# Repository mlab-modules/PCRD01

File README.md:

# PCRD01B
Semiconcductor cosmic radiation detector Silicon diode analogue amplifier.

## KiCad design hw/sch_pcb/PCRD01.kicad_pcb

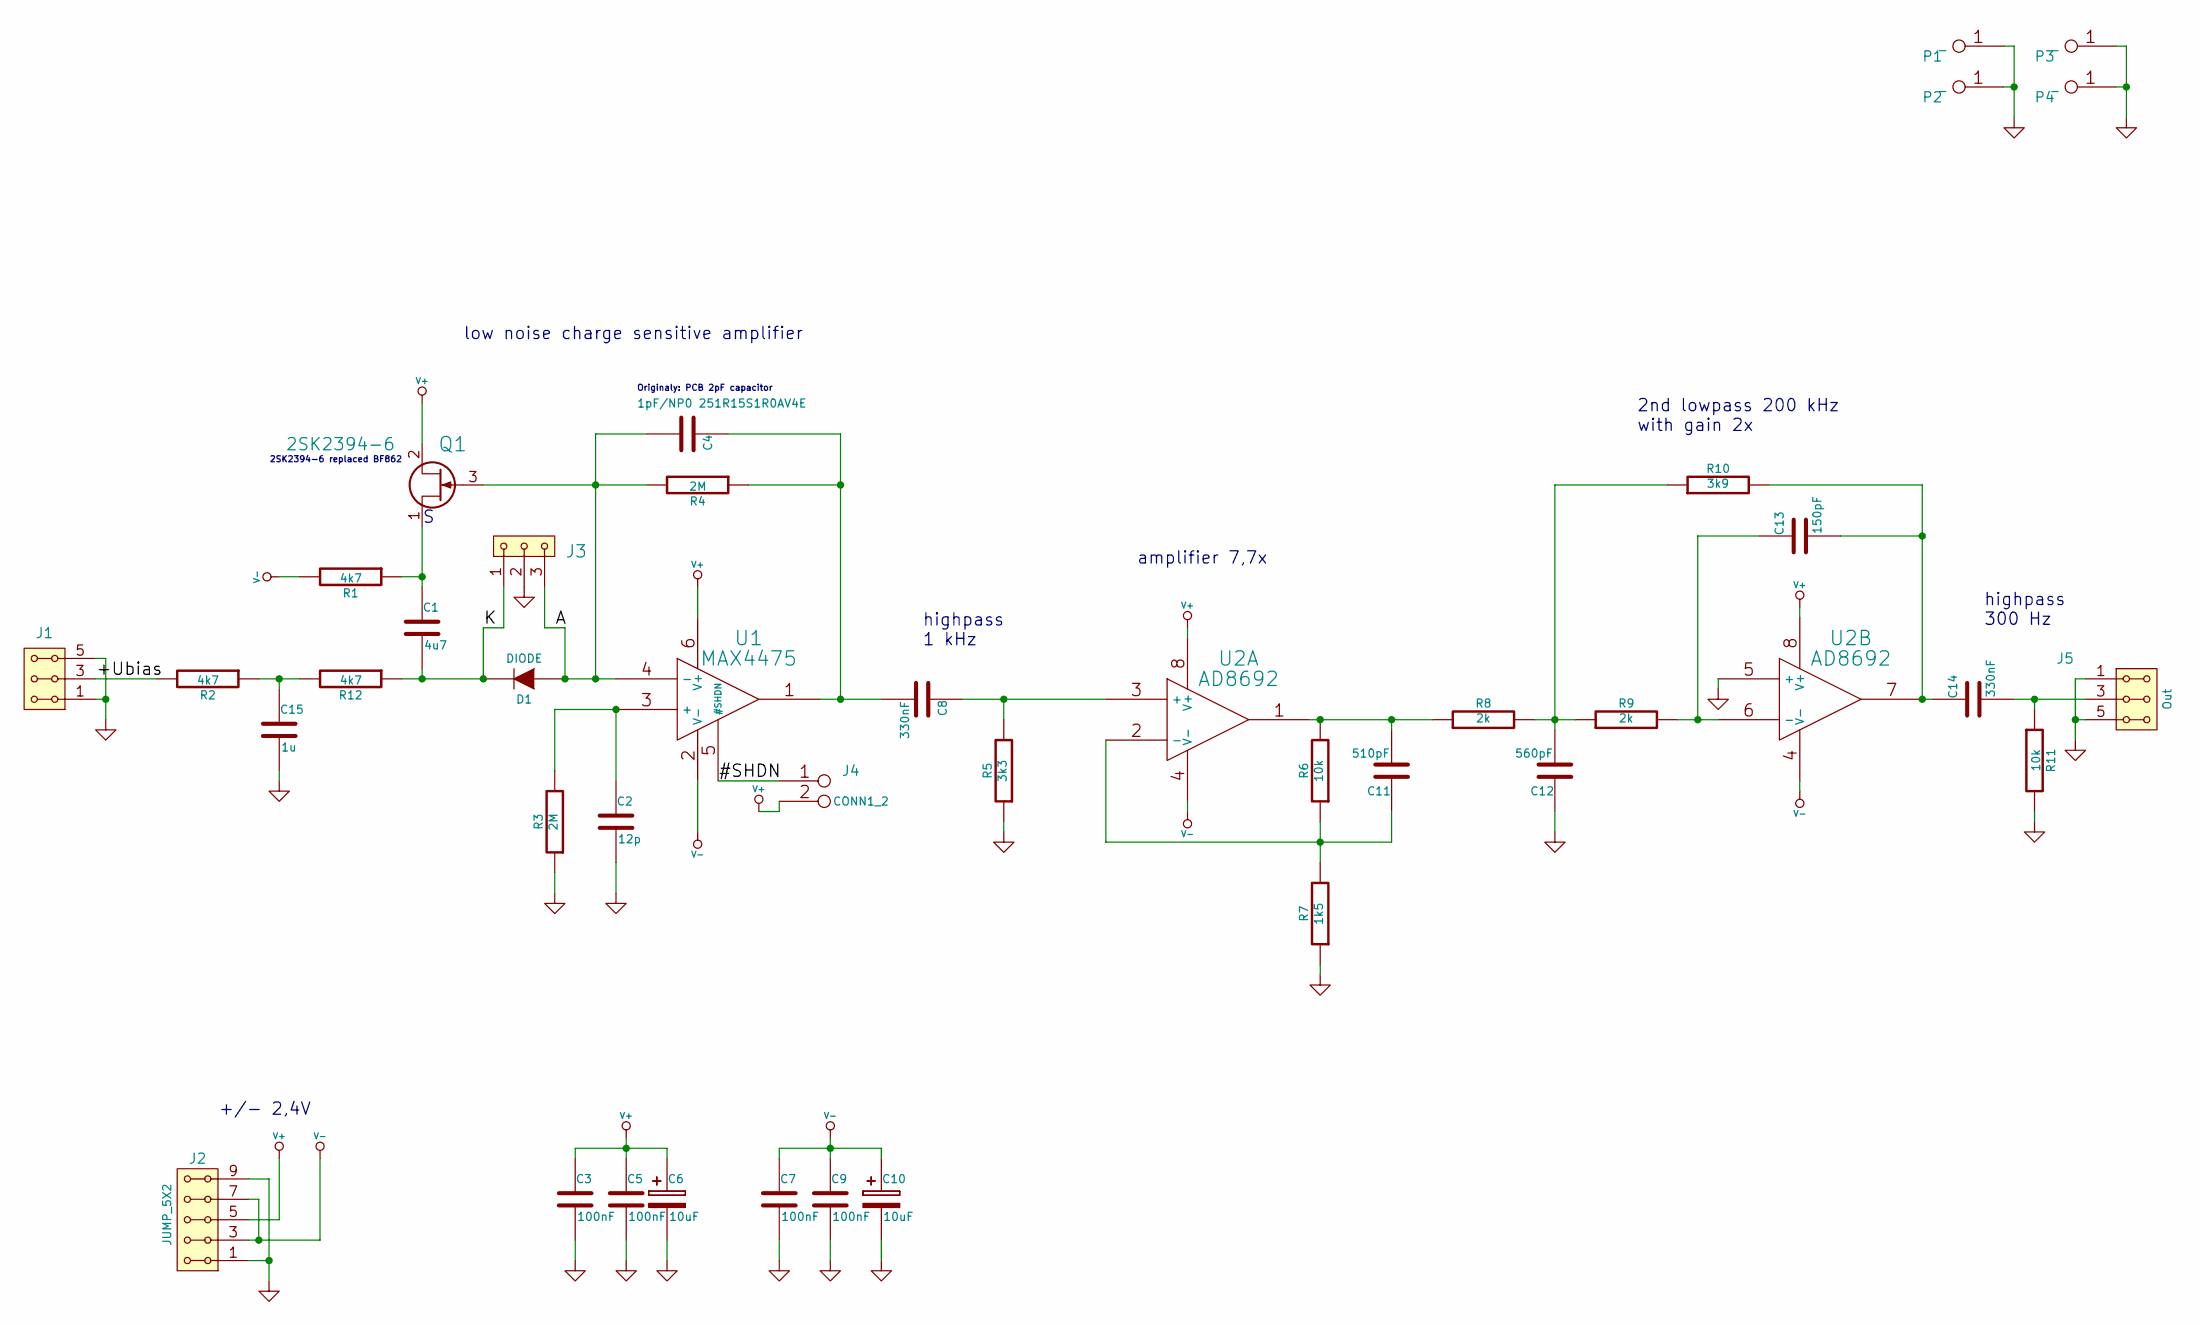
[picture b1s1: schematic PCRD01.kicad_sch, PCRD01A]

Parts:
C1: 4u7; C_0805_2012Metric
C2: 12p; C_0805_2012Metric
C3, C5, C7, C9: 100nF; C_0805_2012Metric
C4: 1pF/NP0 251R15S1R0AV4E; C_0805_2012Metric
C6, C10: 10uF; C_0805_2012Metric
C8, C14: 330nF; C_0805_2012Metric
C11: 510pF; C_0805_2012Metric
C12: 560pF; C_0805_2012Metric
C13: 150pF; C_0805_2012Metric
C15: 1u; C_0805_2012Metric
D1: DIODE
J1: JUMP_3X2; Straight_2x03
J2: JUMP_5X2; Straight_2x05
J3: HEADER_1x03; Straight_1x03
J4: CONN1_2; Straight_1x02
J5: Out; Straight_2x03
P1, P2, P3, P4: _; MountingHole_3mm
Q1: 2SK2394-6; SOT-23
R1, R2, R12: 4k7; R_0805_2012Metric
R3, R4: 2M; R_0805_2012Metric
R5: 3k3; R_0805_2012Metric
R6, R11: 10k; R_0805_2012Metric
R7: 1k5; R_0805_2012Metric
R8, R9: 2k; R_0805_2012Metric
R10: 3k9; R_0805_2012Metric
U1: MAX4475; SOT-23-6
U2: AD8692; SOIC-8-N

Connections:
/#SHDN: J4.1, U1.5 (#SHDN)
/+Ubias: J1.3, J1.4, R2.2
/A: C4.2, D1.1 (A), J3.3, Q1.3 (G), R4.2, U1.4 (-)
/K: C1.2, D1.2 (K), J3.1, R12.1
GND: C2.2, C3.2, C5.2, C6.2, C7.2, C9.2, C10.2, C12.1, C15.2, J1.1, J1.2, J1.5, J1.6, J2.1, J2.2, J2.9, J2.10, J3.2, J5.1, J5.2, J5.5, J5.6, P1.1, P2.1, P3.1, P4.1, R3.1, R5.1, R7.1, R11.2, U2.5 (+)
unnamed: C1.1, Q1.1 (S), R1.1
unnamed: C2.1, R3.2, U1.3 (+)
unnamed: C4.1, C8.2, R4.1, U1.1
unnamed: C8.1, R5.2, U2.3 (+)
unnamed: C11.1, R6.1, R7.2, U2.2 (-)
unnamed: C11.2, R6.2, R8.1, U2.1
unnamed: C12.2, R8.2, R9.1, R10.1
unnamed: C13.1, R9.2, U2.6 (-)
unnamed: C13.2, C14.1, R10.2, U2.7
unnamed: C14.2, J5.3, J5.4, R11.1
unnamed: C15.1, R2.1, R12.2
V+: C3.1, C5.1, C6.1, J2.5, J2.6, J4.2 (PM), Q1.2 (D), U1.6 (V+), U2.8 (V+)
V-: C7.1, C9.1, C10.1, J2.3, J2.4, J2.7, J2.8, R1.2, U1.2 (V-), U2.4 (V-)

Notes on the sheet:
highpass 300 Hz
2nd lowpass 200 kHz with gain 2x
+/- 2,4V
amplifier 7,7x
Originaly: PCB 2pF capacitor
2SK2394-6 replaced BF862
low noise charge sensitive amplifier
highpass 1 kHz

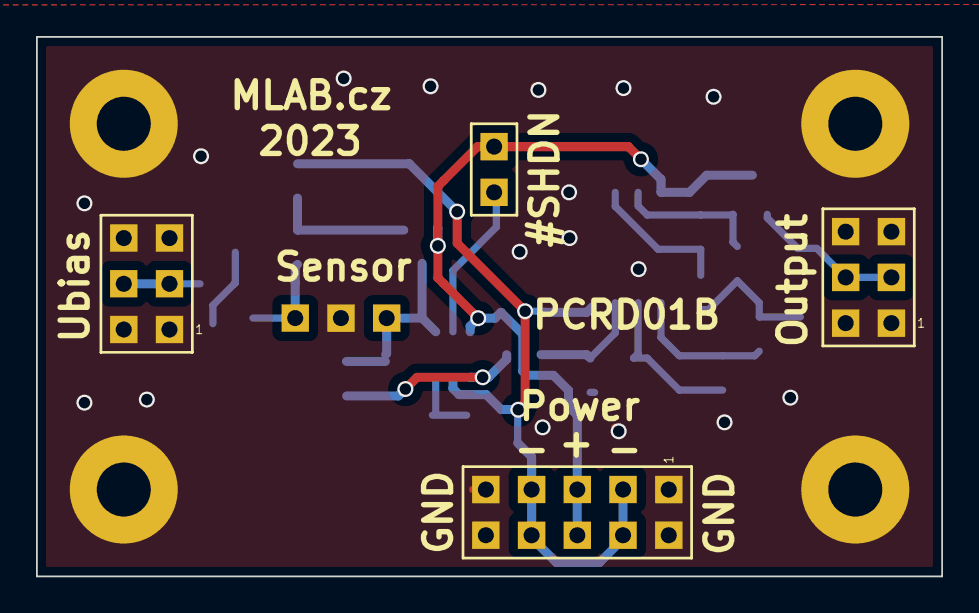
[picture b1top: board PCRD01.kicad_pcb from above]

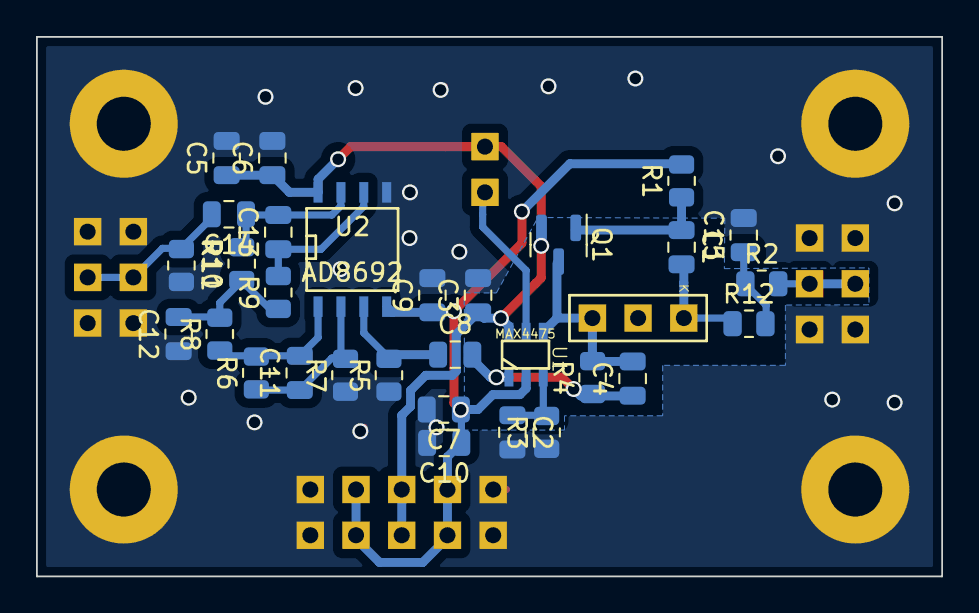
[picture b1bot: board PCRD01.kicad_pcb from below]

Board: 2 copper layers, 50.3 x 30.0 mm, 39 parts (31 on the bottom side), 18 nets.

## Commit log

2017-08-24 Microcontrollers and processors moved to separate directory.
2018-02-15 [MLABweb] 2018-02-15 20:36:39 PCRD01A
2018-02-15 [MLABweb] 2018-02-15 20:36:52 PCRD01A
2018-04-12 [MLABweb] Documentaion edits; PCRD01A
2018-11-05 Presun obrazku do slozky img. Pregenerovani dokumentaci.
2020-11-04 Fix license
2022-02-18 MLAB web edit.
2022-04-06 automated commit; add github actions
2022-04-06 Update actions products
2023-02-14 update actions
2023-02-14 Update metadata files
2023-04-01 Delete TODO.txt
    Rewrite to issue. #1
2023-04-12 convert to kicad 6
2023-04-12 add sheet-stamp
2023-04-12 add ust identificators
2023-04-12 clean layout
2023-04-12 rename id
2023-04-12 replace PCB capacitor
2023-04-12 uklid layoutu
2023-04-12 rename to 01B
2023-04-13 Update workflow files
2023-04-13 Edit PCB
2023-04-13 Fix #2 Add dimensions.
2023-04-13 Disable visibility of irrelevant text.
2023-07-05 automated commit; rename source files to new naming convence
2023-09-16 Update image to image_title
2023-09-16 Update status
